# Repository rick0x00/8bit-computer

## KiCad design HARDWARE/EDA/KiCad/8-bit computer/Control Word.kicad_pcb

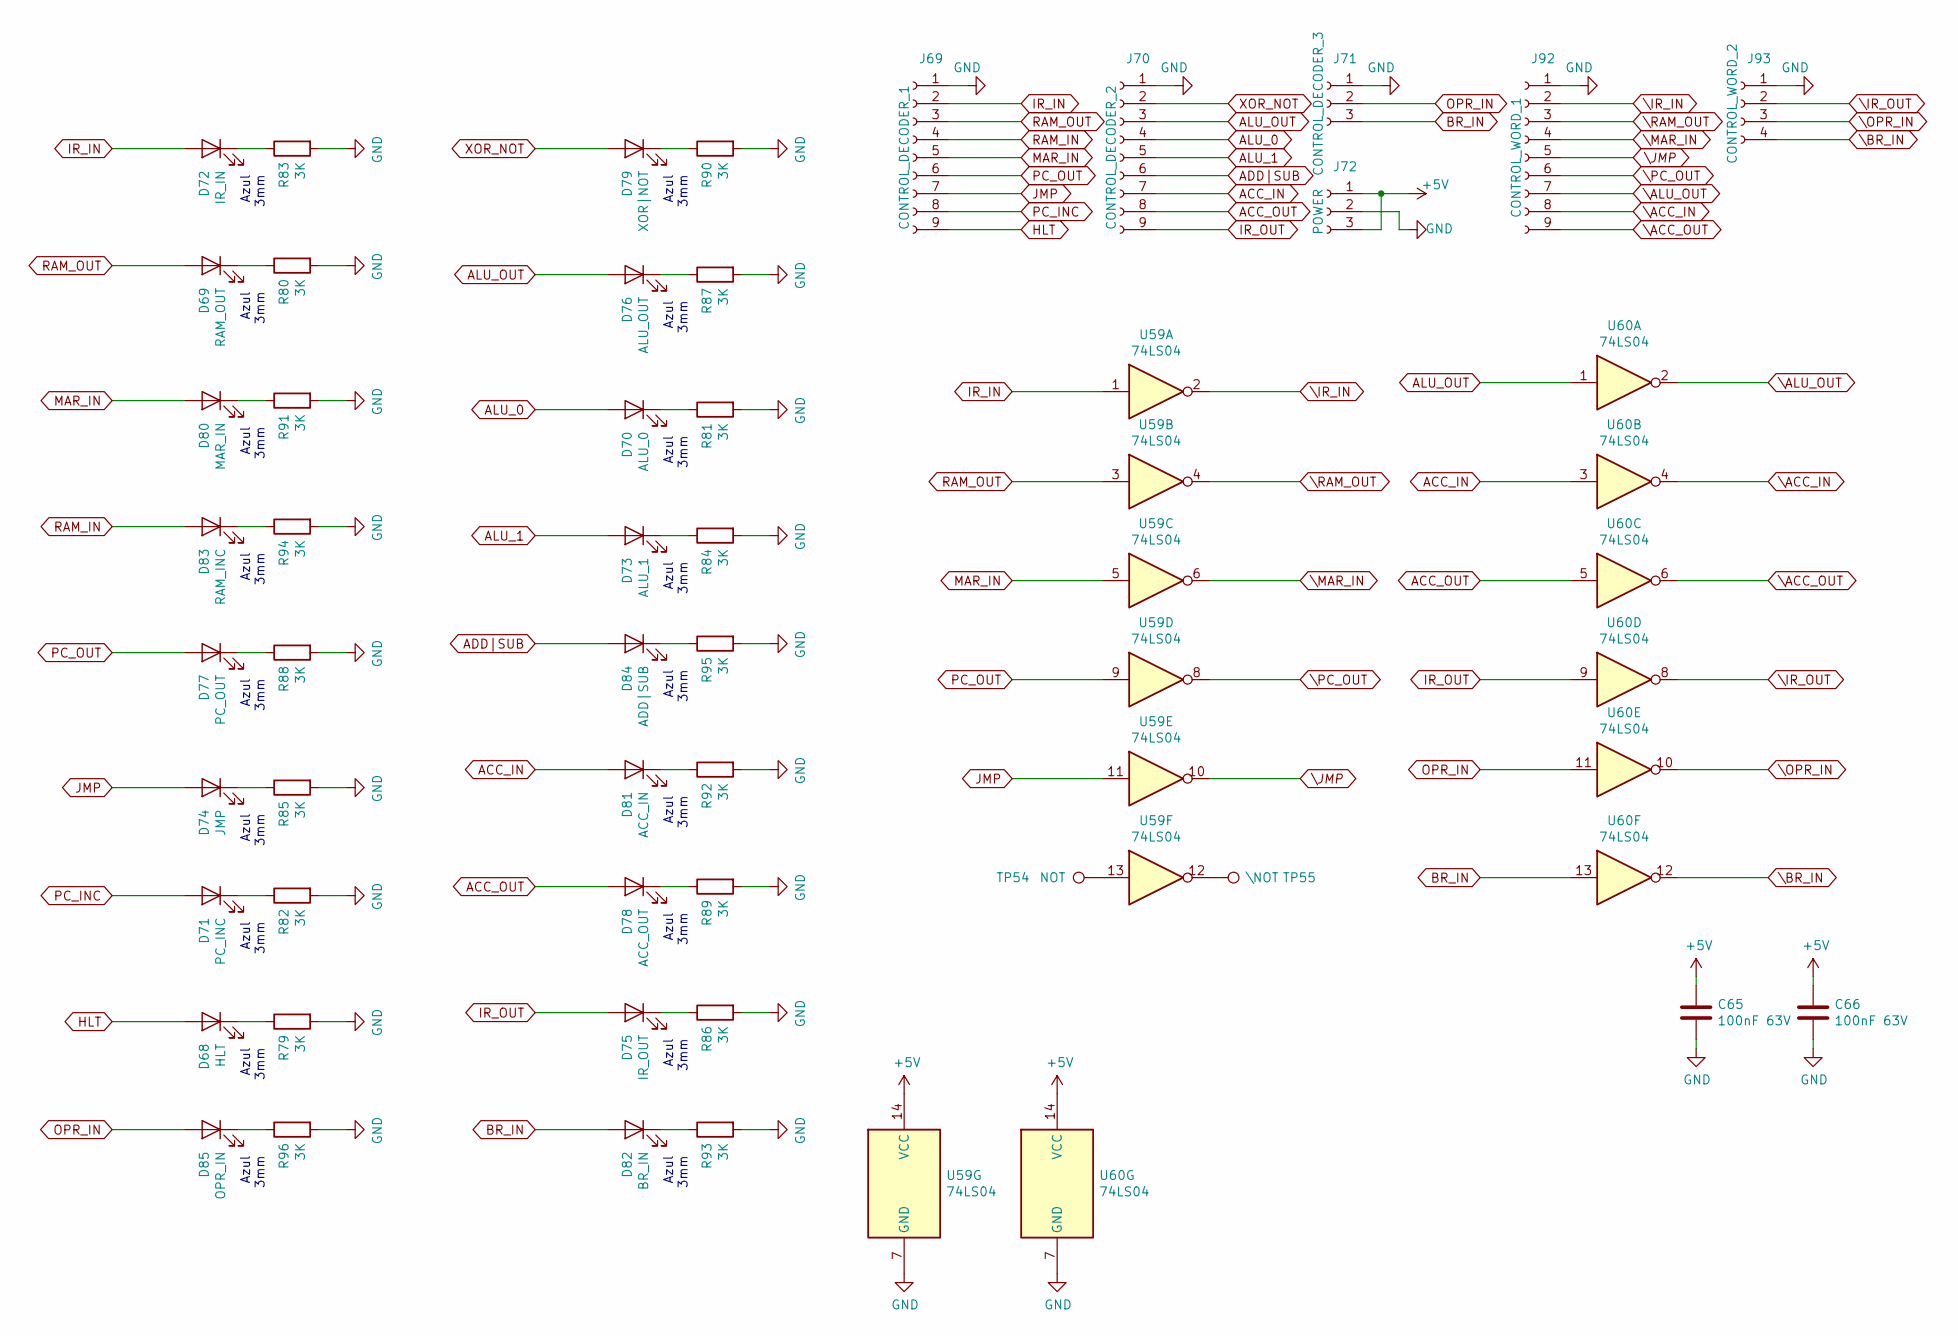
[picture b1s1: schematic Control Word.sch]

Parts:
C65, C66: 100nF 63V; C_Rect_L7.0mm_W2.5mm_P5.00mm
D68: HLT; LED_D3.0mm_Clear
D69: RAM_OUT; LED_D3.0mm_Clear
D70: ALU_0; LED_D3.0mm_Clear
D71: PC_INC; LED_D3.0mm_Clear
D72: IR_IN; LED_D3.0mm_Clear
D73: ALU_1; LED_D3.0mm_Clear
D74: JMP; LED_D3.0mm_Clear
D75: IR_OUT; LED_D3.0mm_Clear
D76: ALU_OUT; LED_D3.0mm_Clear
D77: PC_OUT; LED_D3.0mm_Clear
D78: ACC_OUT; LED_D3.0mm_Clear
D79: XOR|NOT; LED_D3.0mm_Clear
D80: MAR_IN; LED_D3.0mm_Clear
D81: ACC_IN; LED_D3.0mm_Clear
D82: BR_IN; LED_D3.0mm_Clear
D83: RAM_INC; LED_D3.0mm_Clear
D84: ADD|SUB; LED_D3.0mm_Clear
D85: OPR_IN; LED_D3.0mm_Clear
J69: CONTROL_DECODER_1; PinSocket_1x09_P2.00mm_Vertical
J70: CONTROL_DECODER_2; PinSocket_1x09_P2.00mm_Vertical
J71: CONTROL_DECODER_3; PinSocket_1x03_P2.00mm_Vertical
J72: POWER; PinSocket_1x03_P2.00mm_Vertical
J92: CONTROL_WORD_1; PinSocket_1x09_P2.00mm_Vertical
J93: CONTROL_WORD_2; PinSocket_1x04_P2.00mm_Vertical
R79, R80, R81, R82, R83, R84, R85, R86, R87, R88, R89, R90, R91, R92, R93, R94, R95, R96: 3K; R_Axial_DIN0207_L6.3mm_D2.5mm_P7.62mm_Horizontal
TP54: NOT; TestPoint_THTPad_D1.5mm_Drill0.7mm
TP55: \\NOT; TestPoint_THTPad_D1.5mm_Drill0.7mm
U59, U60: 74LS04; DIP-14_W7.62mm_LongPads

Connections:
+5V: C65.1, C66.1, J72.1, J72.3, U59.14 (VCC), U60.14 (VCC)
ACC_IN: D81.2 (A), J70.7, U60.3
ACC_OUT: D78.2 (A), J70.8, U60.5
ADD|SUB: D84.2 (A), J70.6
ALU_0: D70.2 (A), J70.4
ALU_1: D73.2 (A), J70.5
ALU_OUT: D76.2 (A), J70.3, U60.1
BR_IN: D82.2 (A), J71.3, U60.13
GND: C65.2, C66.2, J69.1, J70.1, J71.1, J72.2, J92.1, J93.1, R79.2, R80.2, R81.2, R82.2, R83.2, R84.2, R85.2, R86.2, R87.2, R88.2, R89.2, R90.2, R91.2, R92.2, R93.2, R94.2, R95.2, R96.2, U59.7 (GND), U60.7 (GND)
HLT: D68.2 (A), J69.9
IR_IN: D72.2 (A), J69.2, U59.1
IR_OUT: D75.2 (A), J70.9, U60.9
JMP: D74.2 (A), J69.7, U59.11
MAR_IN: D80.2 (A), J69.5, U59.5
unnamed: D68.1 (K), R79.1
unnamed: D69.1 (K), R80.1
unnamed: D70.1 (K), R81.1
unnamed: D71.1 (K), R82.1
unnamed: D72.1 (K), R83.1
unnamed: D73.1 (K), R84.1
unnamed: D74.1 (K), R85.1
unnamed: D75.1 (K), R86.1
unnamed: D76.1 (K), R87.1
unnamed: D77.1 (K), R88.1
unnamed: D78.1 (K), R89.1
unnamed: D79.1 (K), R90.1
unnamed: D80.1 (K), R91.1
unnamed: D81.1 (K), R92.1
unnamed: D82.1 (K), R93.1
unnamed: D83.1 (K), R94.1
unnamed: D84.1 (K), R95.1
unnamed: D85.1 (K), R96.1
unnamed: TP54.1, U59.13
unnamed: TP55.1, U59.12
OPR_IN: D85.2 (A), J71.2, U60.11
PC_INC: D71.2 (A), J69.8
PC_OUT: D77.2 (A), J69.6, U59.9
RAM_IN: D83.2 (A), J69.4
RAM_OUT: D69.2 (A), J69.3, U59.3
XOR_NOT: D79.2 (A), J70.2
\ACC_IN: J92.8, U60.4
\ACC_OUT: J92.9, U60.6
\ALU_OUT: J92.7, U60.2
\BR_IN: J93.4, U60.12
\IR_IN: J92.2, U59.2
\IR_OUT: J93.2, U60.8
\JMP: J92.5, U59.10
\MAR_IN: J92.4, U59.6
\OPR_IN: J93.3, U60.10
\PC_OUT: J92.6, U59.8
\RAM_OUT: J92.3, U59.4

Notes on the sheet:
Azul 3mm

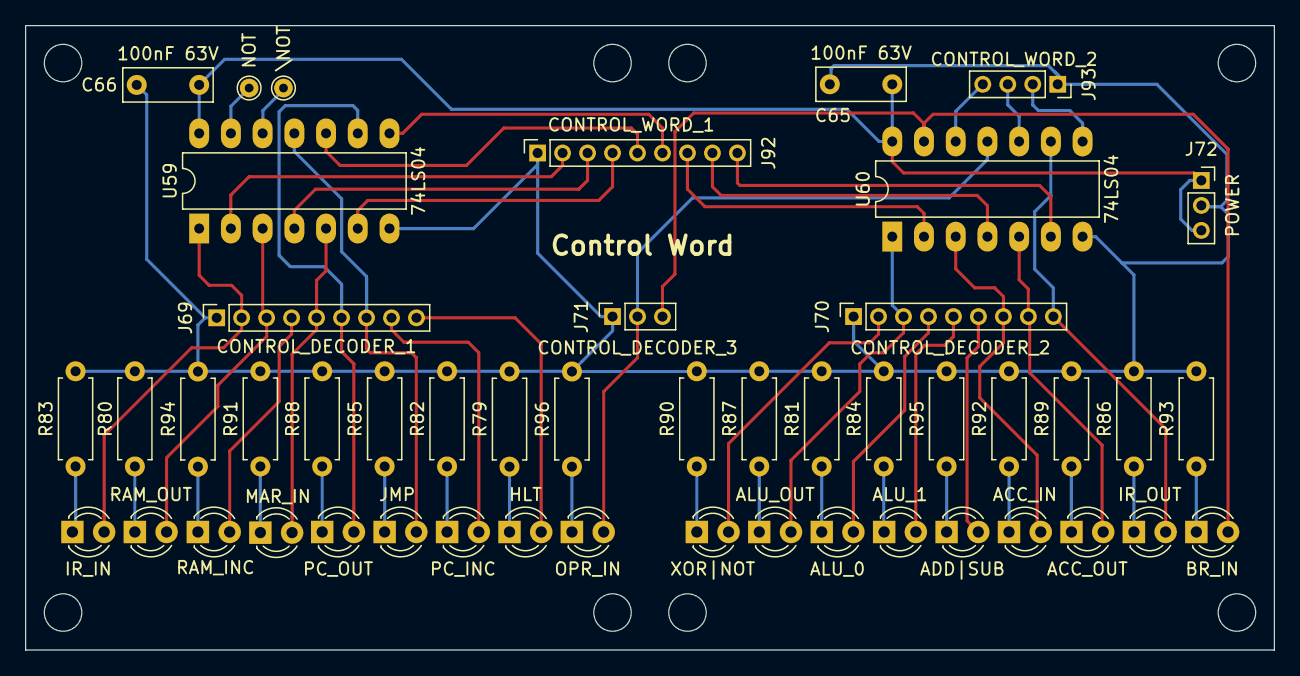
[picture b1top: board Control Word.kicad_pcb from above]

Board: 2 copper layers, 100.0 x 50.0 mm, 48 parts (0 on the bottom side), 51 nets.

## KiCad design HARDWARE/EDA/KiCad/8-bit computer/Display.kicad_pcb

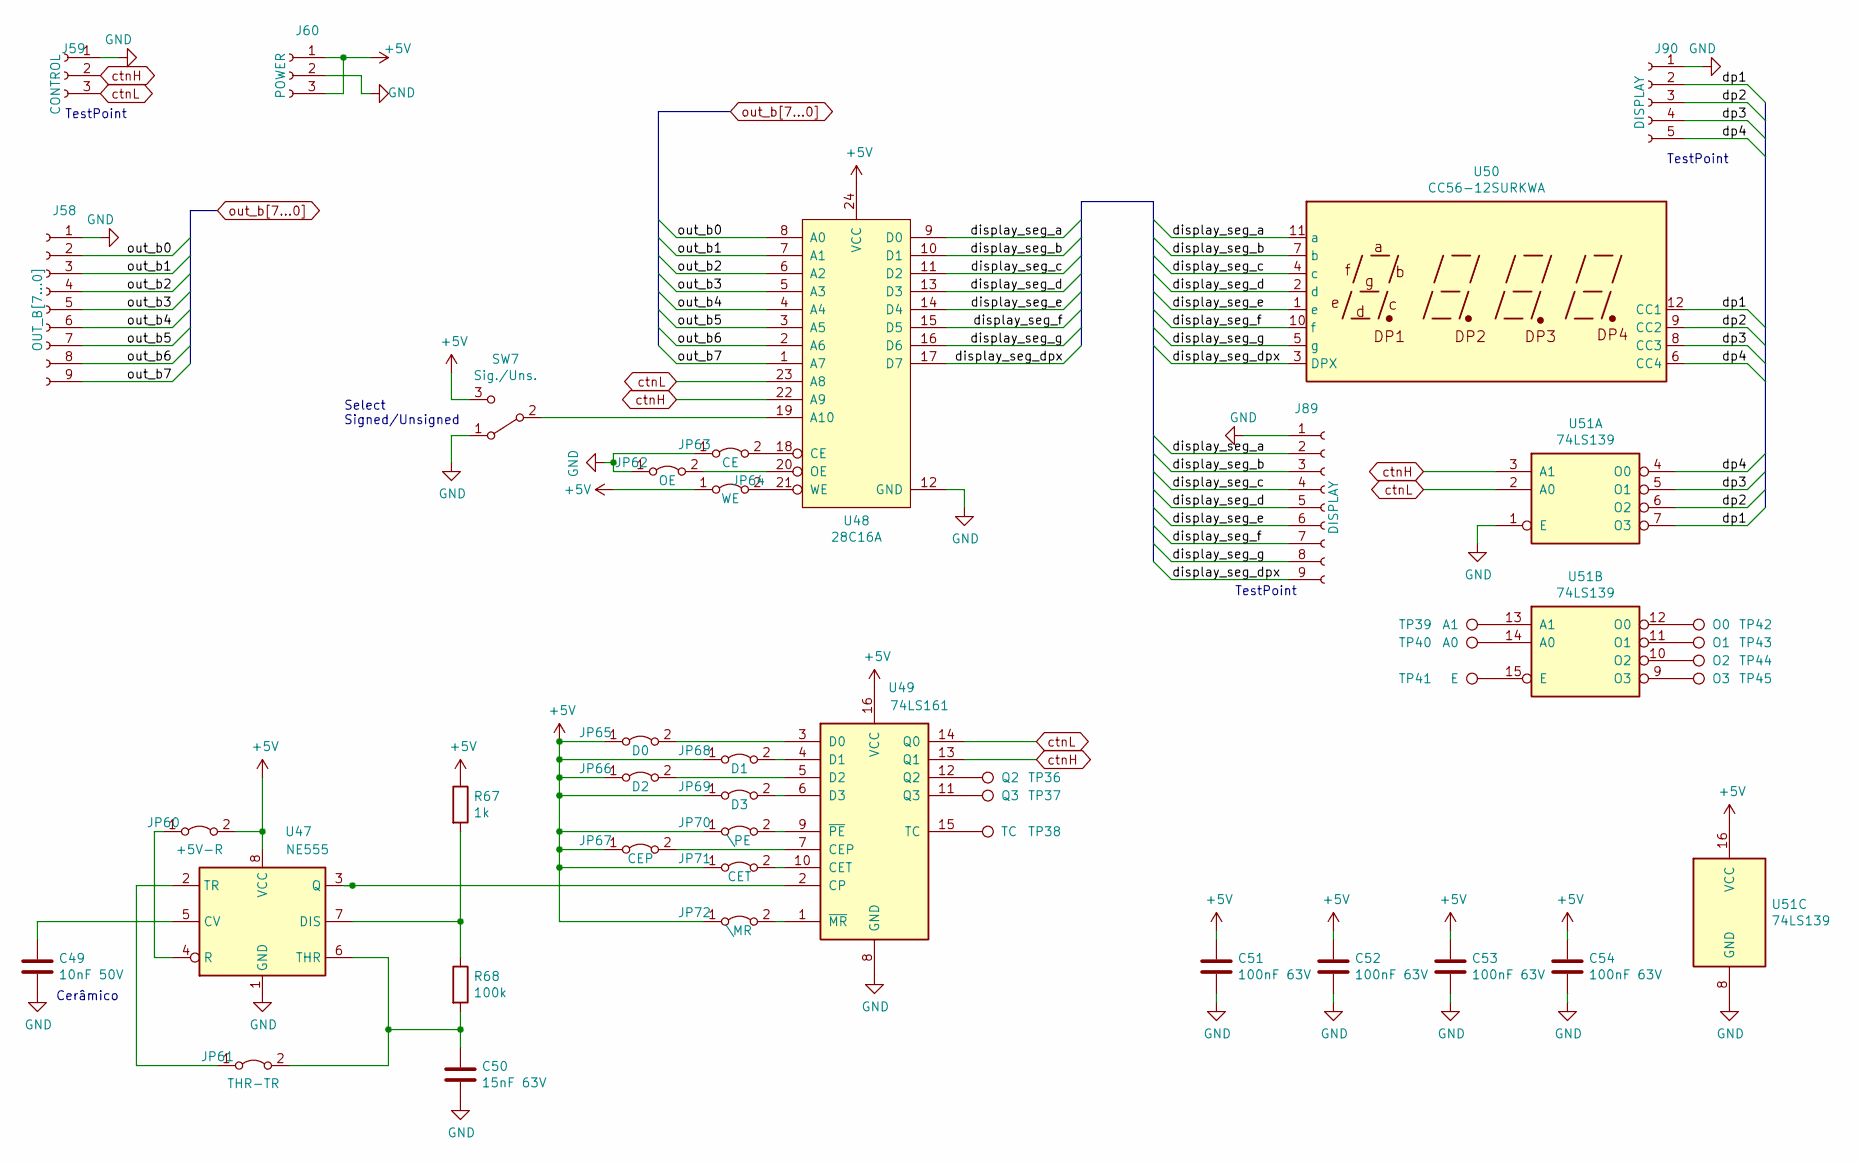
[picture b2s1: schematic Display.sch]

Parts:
C49: 10nF 50V; C_Disc_D4.3mm_W1.9mm_P5.00mm
C50: 15nF 63V; C_Rect_L7.0mm_W2.5mm_P5.00mm
C51, C52, C53, C54: 100nF 63V; C_Rect_L7.0mm_W2.5mm_P5.00mm
J58: OUT_B[7...0]; PinSocket_1x09_P2.00mm_Vertical
J59: CONTROL; PinSocket_1x03_P2.00mm_Vertical
J60: POWER; PinSocket_1x03_P2.00mm_Vertical
J89: DISPLAY; PinSocket_1x09_P2.00mm_Vertical
J90: DISPLAY; PinSocket_1x05_P2.00mm_Vertical
JP60: +5V-R; TestPoint_2Pads_Pitch2.54mm_Drill0.8mm
JP61: THR-TR; TestPoint_2Pads_Pitch2.54mm_Drill0.8mm
JP62: OE; TestPoint_2Pads_Pitch2.54mm_Drill0.8mm
JP63: CE; TestPoint_2Pads_Pitch2.54mm_Drill0.8mm
JP64: WE; TestPoint_2Pads_Pitch2.54mm_Drill0.8mm
JP65: D0; TestPoint_2Pads_Pitch2.54mm_Drill0.8mm
JP66: D2; TestPoint_2Pads_Pitch2.54mm_Drill0.8mm
JP67: CEP; TestPoint_2Pads_Pitch2.54mm_Drill0.8mm
JP68: D1; TestPoint_2Pads_Pitch2.54mm_Drill0.8mm
JP69: D3; TestPoint_2Pads_Pitch2.54mm_Drill0.8mm
JP70: \\PE; TestPoint_2Pads_Pitch2.54mm_Drill0.8mm
JP71: CET; TestPoint_2Pads_Pitch2.54mm_Drill0.8mm
JP72: \\MR; TestPoint_2Pads_Pitch2.54mm_Drill0.8mm
R67: 1k; R_Axial_DIN0207_L6.3mm_D2.5mm_P7.62mm_Horizontal
R68: 100k; R_Axial_DIN0207_L6.3mm_D2.5mm_P7.62mm_Horizontal
SW7: Sig./Uns.; SW_CuK_OS102011MA1QN1_SPDT_Angled
TP36: Q2; TestPoint_THTPad_D1.5mm_Drill0.7mm
TP37: Q3; TestPoint_THTPad_D1.5mm_Drill0.7mm
TP38: TC; TestPoint_THTPad_D1.5mm_Drill0.7mm
TP39: A1; TestPoint_THTPad_D1.5mm_Drill0.7mm
TP40: A0; TestPoint_THTPad_D1.5mm_Drill0.7mm
TP41: E; TestPoint_THTPad_D1.5mm_Drill0.7mm
TP42: O0; TestPoint_THTPad_D1.5mm_Drill0.7mm
TP43: O1; TestPoint_THTPad_D1.5mm_Drill0.7mm
TP44: O2; TestPoint_THTPad_D1.5mm_Drill0.7mm
TP45: O3; TestPoint_THTPad_D1.5mm_Drill0.7mm
U47: NE555; DIP-8_W7.62mm_LongPads
U48: 28C16A; DIP-24_W15.24mm_LongPads
U49: 74LS161; DIP-16_W7.62mm_LongPads
U50: CC56-12SURKWA; CA56-12SURKWA
U51: 74LS139; DIP-16_W7.62mm_LongPads

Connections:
+5V: C51.1, C52.1, C53.1, C54.1, J60.1, J60.3, JP60.2 (B), JP64.1 (A), JP65.1 (A), JP66.1 (A), JP67.1 (A), JP68.1 (A), JP69.1 (A), JP70.1 (A), JP71.1 (A), JP72.1 (A), R67.1, SW7.3 (C), U47.8 (VCC), U48.24 (VCC), U49.16 (VCC), U51.16 (VCC)
/display_seg_a: J89.2, U48.9 (D0), U50.11 (a)
/display_seg_b: J89.3, U48.10 (D1), U50.7 (b)
/display_seg_c: J89.4, U48.11 (D2), U50.4 (c)
/display_seg_d: J89.5, U48.13 (D3), U50.2 (d)
/display_seg_dpx: J89.9, U48.17 (D7), U50.3 (DPX)
/display_seg_e: J89.6, U48.14 (D4), U50.1 (e)
/display_seg_f: J89.7, U48.15 (D5), U50.10 (f)
/display_seg_g: J89.8, U48.16 (D6), U50.5 (g)
/dp1: J90.2, U50.12 (CC1), U51.7 (O3)
/dp2: J90.3, U50.9 (CC2), U51.6 (O2)
/dp3: J90.4, U50.8 (CC3), U51.5 (O1)
/dp4: J90.5, U50.6 (CC4), U51.4 (O0)
GND: C49.2, C50.2, C51.2, C52.2, C53.2, C54.2, J58.1, J59.1, J60.2, J89.1, J90.1, JP62.1 (A), JP63.1 (A), SW7.1 (A), U47.1 (GND), U48.12 (GND), U49.8 (GND), U51.1 (E), U51.8 (GND)
unnamed: C49.1, U47.5 (CV)
unnamed: C50.1, JP61.2 (B), R68.2, U47.6 (THR)
unnamed: JP60.1 (A), U47.4 (R)
unnamed: JP61.1 (A), U47.2 (TR)
unnamed: JP62.2 (B), U48.20 (OE)
unnamed: JP63.2 (B), U48.18 (CE)
unnamed: JP64.2 (B), U48.21 (WE)
unnamed: JP65.2 (B), U49.3 (D0)
unnamed: JP66.2 (B), U49.5 (D2)
unnamed: JP67.2 (B), U49.7 (CEP)
unnamed: JP68.2 (B), U49.4 (D1)
unnamed: JP69.2 (B), U49.6 (D3)
unnamed: JP70.2 (B), U49.9 (~PE)
unnamed: JP71.2 (B), U49.10 (CET)
unnamed: JP72.2 (B), U49.1 (~MR)
unnamed: R67.2, R68.1, U47.7 (DIS)
unnamed: SW7.2 (B), U48.19 (A10)
unnamed: TP36.1, U49.12 (Q2)
unnamed: TP37.1, U49.11 (Q3)
unnamed: TP38.1, U49.15 (TC)
unnamed: TP39.1, U51.13 (A1)
unnamed: TP40.1, U51.14 (A0)
unnamed: TP41.1, U51.15 (E)
unnamed: TP42.1, U51.12 (O0)
unnamed: TP43.1, U51.11 (O1)
unnamed: TP44.1, U51.10 (O2)
unnamed: TP45.1, U51.9 (O3)
unnamed: U47.3 (Q), U49.2 (CP)
ctnH: J59.2, U48.22 (A9), U49.13 (Q1), U51.3 (A1)
ctnL: J59.3, U48.23 (A8), U49.14 (Q0), U51.2 (A0)
out_b0: J58.2, U48.8 (A0)
out_b1: J58.3, U48.7 (A1)
out_b2: J58.4, U48.6 (A2)
out_b3: J58.5, U48.5 (A3)
out_b4: J58.6, U48.4 (A4)
out_b5: J58.7, U48.3 (A5)
out_b6: J58.8, U48.2 (A6)
out_b7: J58.9, U48.1 (A7)

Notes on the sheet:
Select Signed/Unsigned
Cerâmico
TestPoint

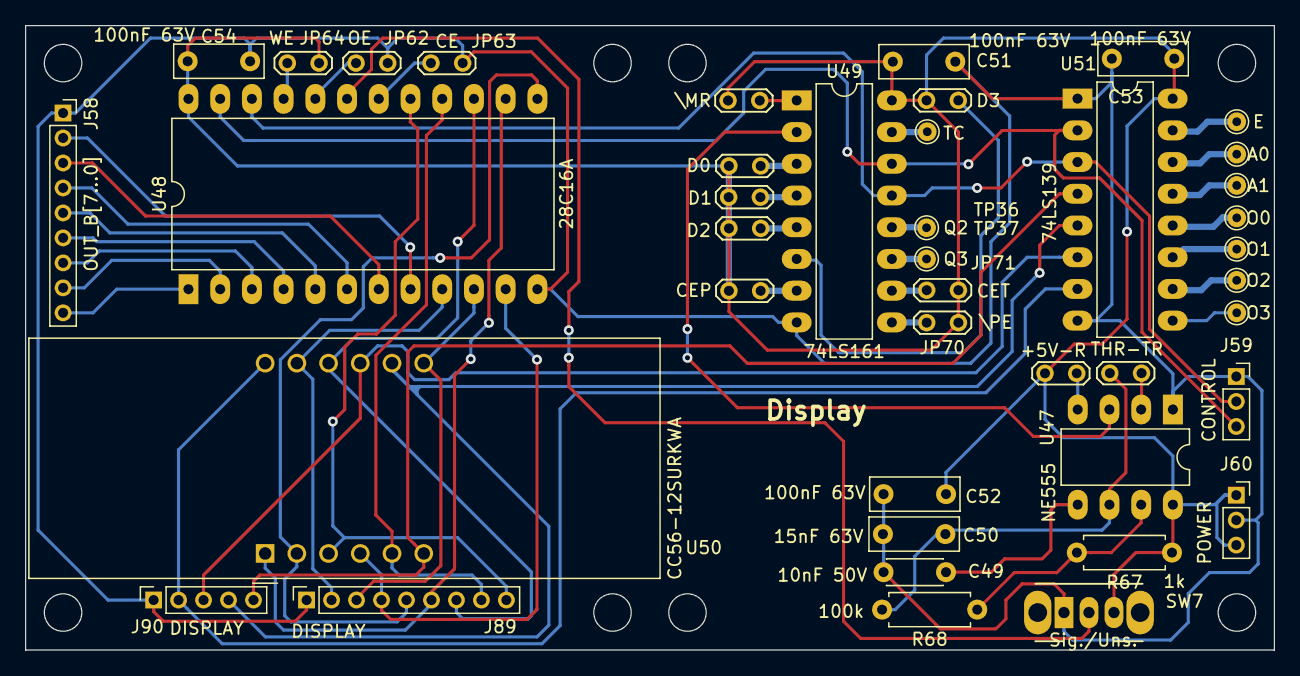
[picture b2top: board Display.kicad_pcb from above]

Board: 2 copper layers, 100.0 x 50.0 mm, 42 parts (0 on the bottom side), 52 nets.

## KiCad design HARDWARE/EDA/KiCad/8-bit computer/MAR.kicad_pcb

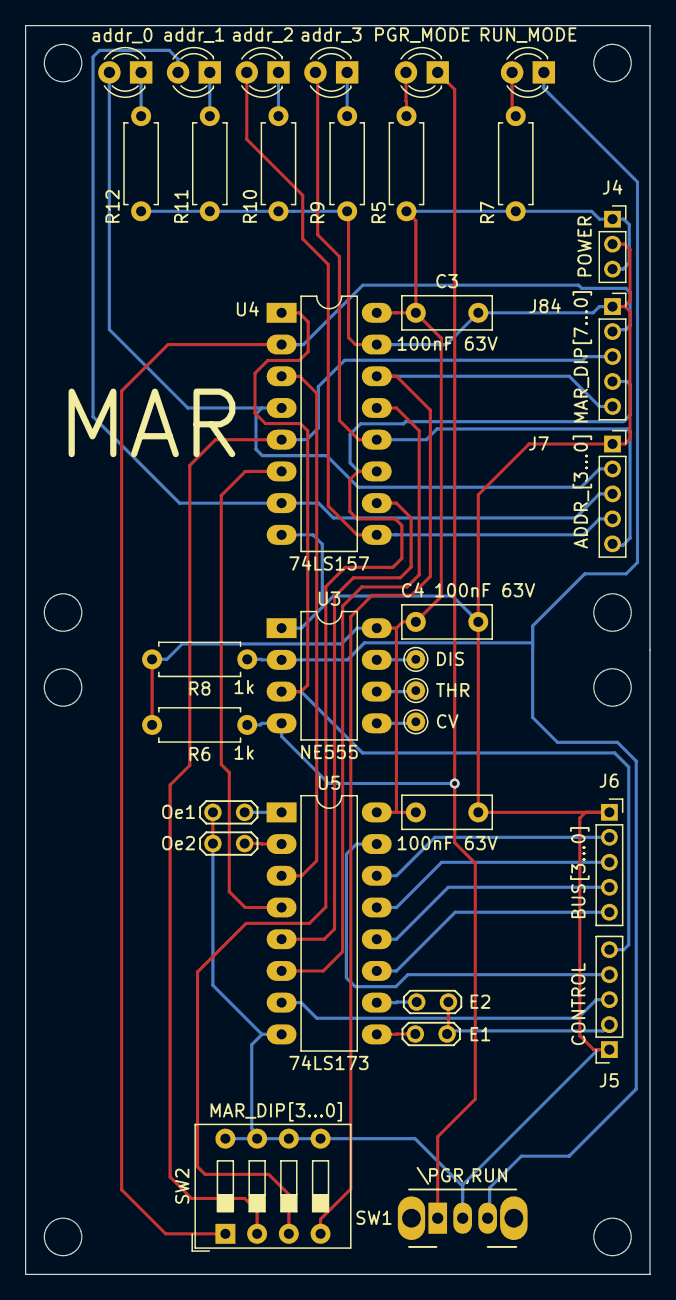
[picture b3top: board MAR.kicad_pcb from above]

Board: 2 copper layers, 50.0 x 100.0 mm, 34 parts (0 on the bottom side), 37 nets.

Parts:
C3, C4, C5: 100nF 63V; C_Rect_L7.0mm_W2.5mm_P5.00mm
D5: PGR_MODE; LED_D3.0mm
D6: RUN_MODE; LED_D3.0mm
D7: addr_3; LED_D3.0mm
D8: addr_2; LED_D3.0mm
D9: addr_1; LED_D3.0mm
D10: addr_0; LED_D3.0mm
J4: POWER; PinSocket_1x03_P2.00mm_Vertical
J5: CONTROL; PinSocket_1x05_P2.00mm_Vertical
J6: BUS[3...0]; PinSocket_1x05_P2.00mm_Vertical
J7: ADDR_[3...0]; PinSocket_1x05_P2.00mm_Vertical
J84: MAR_DIP[7...0]; PinSocket_1x05_P2.00mm_Vertical
JP8: Oe1; TestPoint_2Pads_Pitch2.54mm_Drill0.8mm
JP9: E2; TestPoint_2Pads_Pitch2.54mm_Drill0.8mm
JP10: Oe2; TestPoint_2Pads_Pitch2.54mm_Drill0.8mm
JP11: E1; TestPoint_2Pads_Pitch2.54mm_Drill0.8mm
R5, R7: 470; R_Axial_DIN0207_L6.3mm_D2.5mm_P7.62mm_Horizontal
R6, R8: 1k; R_Axial_DIN0207_L6.3mm_D2.5mm_P7.62mm_Horizontal
R9, R10, R11, R12: 150; R_Axial_DIN0207_L6.3mm_D2.5mm_P7.62mm_Horizontal
SW1: \PGR,RUN; SW_CuK_OS102011MA1QN1_SPDT_Angled
SW2: MAR_DIP[3...0]; SW_DIP_SPSTx04_Slide_9.78x12.34mm_W7.62mm_P2.54mm
TP6: CV; TestPoint_THTPad_D1.5mm_Drill0.7mm
TP7: DIS; TestPoint_THTPad_D1.5mm_Drill0.7mm
TP8: THR; TestPoint_THTPad_D1.5mm_Drill0.7mm
U3: NE555; DIP-8_W7.62mm_LongPads
U4: 74LS157; DIP-16_W7.62mm_LongPads
U5: 74LS173; DIP-16_W7.62mm_LongPads

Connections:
+5V: C3.1, C4.1, C5.1, J4.1, J4.3, R5.1, R6.2, R7.2, R8.2, U3.8, U4.16, U5.16
/mar_b0: U4.3, U5.3
/mar_b1: U4.6, U5.4
/mar_b2: U4.10, U5.5
/mar_b3: U4.13, U5.6
CLOCK: J5.3, U5.7
GND: C3.2, C4.2, C5.2, J4.2, J5.1, J6.1, J7.1, J84.1, JP8.1, JP10.1, R9.2, R10.2, R11.2, R12.2, SW1.2, SW2.5, SW2.6, SW2.7, SW2.8, U3.1, U4.8, U4.15, U5.8
unnamed: D5.1, R6.1, SW1.1, U3.4
unnamed: D5.2, R5.2
unnamed: D6.1, R8.1, SW1.3, U3.2
unnamed: D6.2, R7.1
unnamed: D7.1, R9.1
unnamed: D8.1, R10.1
unnamed: D9.1, R11.1
unnamed: D10.1, R12.1
unnamed: JP8.2, U5.1
unnamed: JP9.2, U5.10
unnamed: JP10.2, U5.2
unnamed: JP11.2, U5.9
unnamed: TP6.1, U3.5
unnamed: TP7.1, U3.7
unnamed: TP8.1, U3.6
RESET: J5.4, U5.15
\MAR_IN: J5.2, JP9.1, JP11.1
\Program,Run: J5.5, U3.3, U4.1
addr_0: D10.2, J7.2, U4.4
addr_1: D9.2, J7.3, U4.7
addr_2: D8.2, J7.4, U4.9
addr_3: D7.2, J7.5, U4.12
bus0: J6.2, U5.14
bus1: J6.3, U5.13
bus2: J6.4, U5.12
bus3: J6.5, U5.11
mar_dip0: J84.2, SW2.1, U4.2
mar_dip1: J84.3, SW2.2, U4.5
mar_dip2: J84.4, SW2.3, U4.11
mar_dip3: J84.5, SW2.4, U4.14

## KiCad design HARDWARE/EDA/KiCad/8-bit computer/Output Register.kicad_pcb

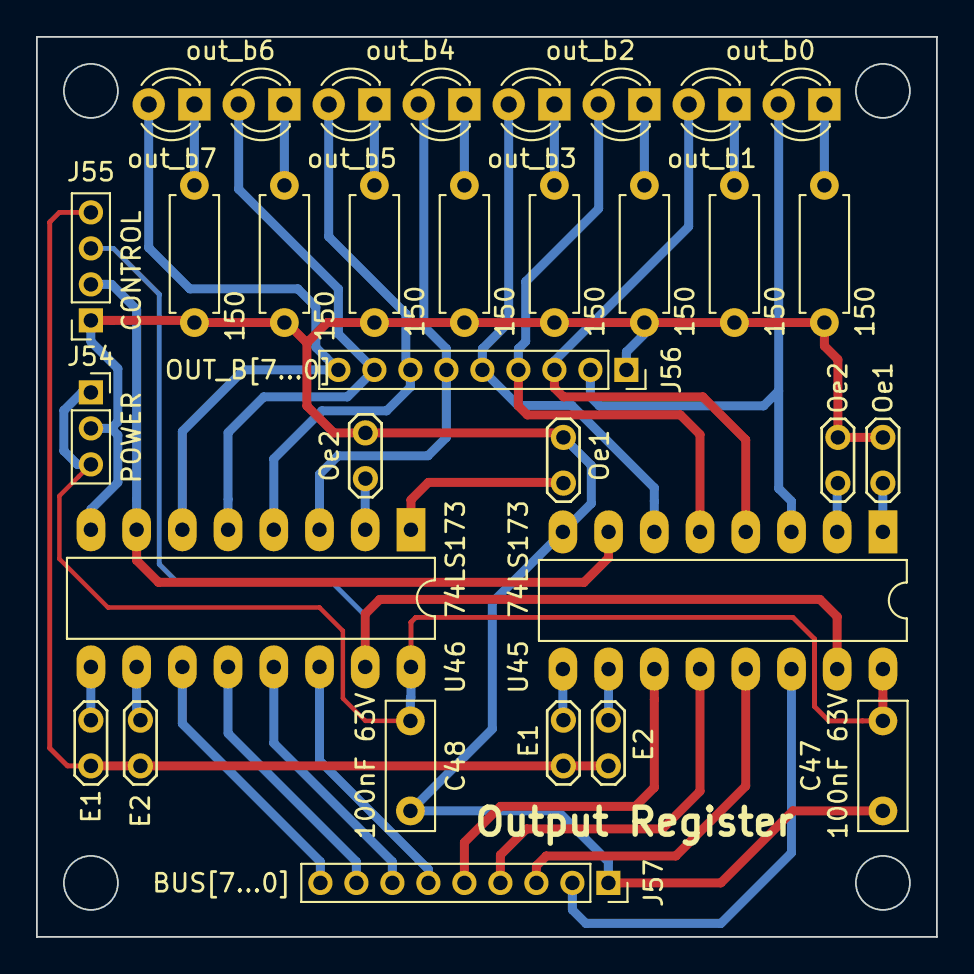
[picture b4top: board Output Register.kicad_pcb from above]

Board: 2 copper layers, 50.0 x 50.0 mm, 32 parts (0 on the bottom side), 37 nets.

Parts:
C47, C48: 100nF 63V; C_Rect_L7.0mm_W2.5mm_P5.00mm
D51: out_b7; LED_D3.0mm_Clear
D52: out_b6; LED_D3.0mm_Clear
D53: out_b5; LED_D3.0mm_Clear
D54: out_b4; LED_D3.0mm_Clear
D55: out_b3; LED_D3.0mm_Clear
D56: out_b2; LED_D3.0mm_Clear
D57: out_b1; LED_D3.0mm_Clear
D58: out_b0; LED_D3.0mm_Clear
J54: POWER; PinSocket_1x03_P2.00mm_Vertical
J55: CONTROL; PinSocket_1x04_P2.00mm_Vertical
J56: OUT_B[7...0]; PinSocket_1x09_P2.00mm_Vertical
J57: BUS[7...0]; PinSocket_1x09_P2.00mm_Vertical
JP52, JP54: Oe2; TestPoint_2Pads_Pitch2.54mm_Drill0.8mm
JP53, JP55: E2; TestPoint_2Pads_Pitch2.54mm_Drill0.8mm
JP56, JP58: Oe1; TestPoint_2Pads_Pitch2.54mm_Drill0.8mm
JP57, JP59: E1; TestPoint_2Pads_Pitch2.54mm_Drill0.8mm
R59, R60, R61, R62, R63, R64, R65, R66: 150; R_Axial_DIN0207_L6.3mm_D2.5mm_P7.62mm_Horizontal
U45, U46: 74LS173; DIP-16_W7.62mm_LongPads

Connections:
+5V: C47.1, C48.1, J54.1, J54.3, U45.16, U46.16
CLOCK: J55.2, U45.7, U46.7
GND: C47.2, C48.2, J54.2, J55.1, J56.1, J57.1, JP52.1, JP54.1, JP56.1, JP58.1, R59.2, R60.2, R61.2, R62.2, R63.2, R64.2, R65.2, R66.2, U45.8, U46.8
unnamed: D51.1, R59.1
unnamed: D52.1, R60.1
unnamed: D53.1, R61.1
unnamed: D54.1, R62.1
unnamed: D55.1, R63.1
unnamed: D56.1, R64.1
unnamed: D57.1, R65.1
unnamed: D58.1, R66.1
unnamed: JP52.2, U45.2
unnamed: JP53.2, U45.10
unnamed: JP54.2, U46.2
unnamed: JP55.2, U46.10
unnamed: JP56.2, U45.1
unnamed: JP57.2, U45.9
unnamed: JP58.2, U46.1
unnamed: JP59.2, U46.9
RESET: J55.3, U45.15, U46.15
\OPR_IN: J55.4, JP53.1, JP55.1, JP57.1, JP59.1
bus0: J57.2, U45.14
bus1: J57.3, U45.13
bus2: J57.4, U45.12
bus3: J57.5, U45.11
bus4: J57.6, U46.14
bus5: J57.7, U46.13
bus6: J57.8, U46.12
bus7: J57.9, U46.11
out_b0: D58.2, J56.2, U45.3
out_b1: D57.2, J56.3, U45.4
out_b2: D56.2, J56.4, U45.5
out_b3: D55.2, J56.5, U45.6
out_b4: D54.2, J56.6, U46.3
out_b5: D53.2, J56.7, U46.4
out_b6: D52.2, J56.8, U46.5
out_b7: D51.2, J56.9, U46.6

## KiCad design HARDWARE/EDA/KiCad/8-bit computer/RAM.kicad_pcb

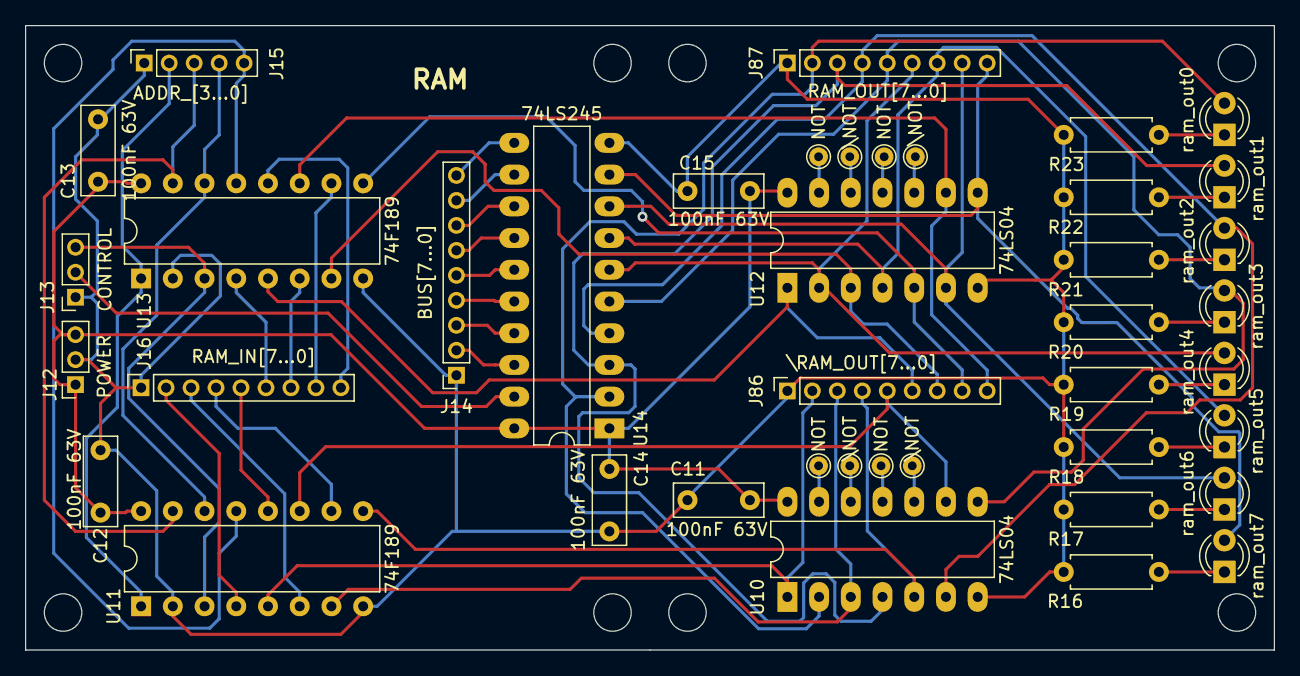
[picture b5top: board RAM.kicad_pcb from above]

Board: 2 copper layers, 100.0 x 50.0 mm, 41 parts (0 on the bottom side), 56 nets.

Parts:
C11, C12, C13, C14, C15: 100nF 63V; C_Rect_L7.0mm_W2.5mm_P5.00mm
D11: ram_out7; LED_D3.0mm
D12: ram_out6; LED_D3.0mm
D13: ram_out5; LED_D3.0mm
D14: ram_out4; LED_D3.0mm
D15: ram_out3; LED_D3.0mm
D16: ram_out2; LED_D3.0mm
D17: ram_out1; LED_D3.0mm
D18: ram_out0; LED_D3.0mm
J12: POWER; PinSocket_1x03_P2.00mm_Vertical
J13: CONTROL; PinSocket_1x03_P2.00mm_Vertical
J14: BUS[7...0]; PinSocket_1x09_P2.00mm_Vertical
J15: ADDR_[3...0]; PinSocket_1x05_P2.00mm_Vertical
J16: RAM_IN[7...0]; PinSocket_1x09_P2.00mm_Vertical
J86: \RAM_OUT[7...0]; PinSocket_1x09_P2.00mm_Vertical
J87: RAM_OUT[7...0]; PinSocket_1x09_P2.00mm_Vertical
R16, R17, R18, R19, R20, R21, R22, R23: 470; R_Axial_DIN0207_L6.3mm_D2.5mm_P7.62mm_Horizontal
TP18, TP19, TP22, TP23: NOT; TestPoint_THTPad_D1.5mm_Drill0.7mm
TP20, TP21, TP24, TP25: \NOT; TestPoint_THTPad_D1.5mm_Drill0.7mm
U10, U12: 74LS04; DIP-14_W7.62mm_LongPads
U11, U13: 74F189; DIP-16_W7.62mm
U14: 74LS245; DIP-20_W7.62mm_LongPads

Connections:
+5V: C11.1, C12.1, C13.1, C14.1, C15.1, J12.1, J12.3, U10.14, U11.16, U12.14, U13.16, U14.1, U14.20
/\ram_out0: J86.2, U10.1, U11.5
/\ram_out1: J86.3, U10.3, U11.7
/\ram_out2: J86.4, U10.5, U11.9
/\ram_out3: J86.5, U10.9, U11.11
/\ram_out4: J86.6, U12.1, U13.5
/\ram_out5: J86.7, U12.3, U13.7
/\ram_out6: J86.8, U12.5, U13.9
/\ram_out7: J86.9, U12.9, U13.11
/ram_out0: D18.2, J87.2, U10.2, U14.2
/ram_out1: D17.2, J87.3, U10.4, U14.3
/ram_out2: D16.2, J87.4, U10.6, U14.4
/ram_out3: D15.2, J87.5, U10.8, U14.5
/ram_out4: D14.2, J87.6, U12.2, U14.6
/ram_out5: D13.2, J87.7, U12.4, U14.7
/ram_out6: D12.2, J87.8, U12.6, U14.8
/ram_out7: D11.2, J87.9, U12.8, U14.9
GND: C11.2, C12.2, C13.2, C14.2, C15.2, J12.2, J13.1, J14.1, J15.1, J16.1, J86.1, J87.1, R16.2, R17.2, R18.2, R19.2, R20.2, R21.2, R22.2, R23.2, U10.7, U11.2, U11.8, U12.7, U13.2, U13.8, U14.10
unnamed: D11.1, R16.1
unnamed: D12.1, R17.1
unnamed: D13.1, R18.1
unnamed: D14.1, R19.1
unnamed: D15.1, R20.1
unnamed: D16.1, R21.1
unnamed: D17.1, R22.1
unnamed: D18.1, R23.1
unnamed: TP18.1, U10.11
unnamed: TP19.1, U10.13
unnamed: TP20.1, U10.10
unnamed: TP21.1, U10.12
unnamed: TP22.1, U12.11
unnamed: TP23.1, U12.13
unnamed: TP24.1, U12.10
unnamed: TP25.1, U12.12
\RAM_OUT: J13.2, U14.19
\WE: J13.3, U11.3, U13.3
addr_0: J15.2, U11.1, U13.1
addr_1: J15.3, U11.15, U13.15
addr_2: J15.4, U11.14, U13.14
addr_3: J15.5, U11.13, U13.13
bus0: J14.2, U14.18
bus1: J14.3, U14.17
bus2: J14.4, U14.16
bus3: J14.5, U14.15
bus4: J14.6, U14.14
bus5: J14.7, U14.13
bus6: J14.8, U14.12
bus7: J14.9, U14.11
ram_in0: J16.2, U11.4
ram_in1: J16.3, U11.6
ram_in2: J16.4, U11.10
ram_in3: J16.5, U11.12
ram_in4: J16.6, U13.4
ram_in5: J16.7, U13.6
ram_in6: J16.8, U13.10
ram_in7: J16.9, U13.12
